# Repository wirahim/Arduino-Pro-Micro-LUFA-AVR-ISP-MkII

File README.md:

# Arduino Pro Micro LUFA AVR ISP MkII

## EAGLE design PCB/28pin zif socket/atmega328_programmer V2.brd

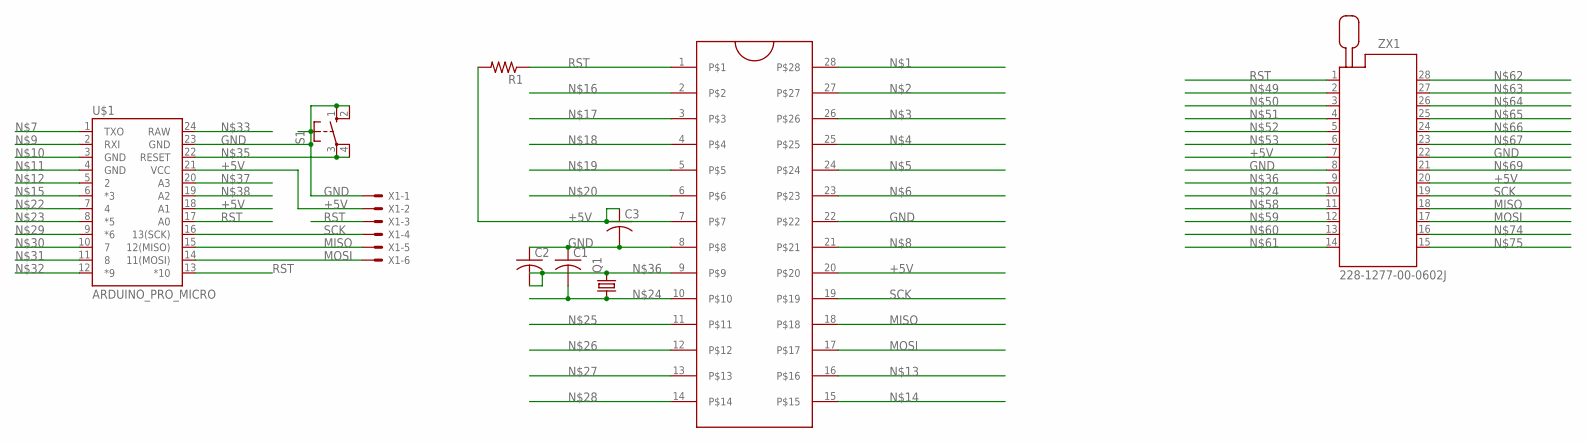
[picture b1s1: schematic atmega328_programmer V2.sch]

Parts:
C1, C2, C3: C-US025-024X044; C025-024X044
Q1: CRYSTALHC49U-V; HC49U-V
R1: R-US_0207/10; 0207/10
S1: 10-XX; B3F-10XX
U$1: ARDUINO_PRO_MICRO
U$2: ZIFSOCKET-28-3ZIFFSOCKET-28-3; DIL28-3-ZIF_SOCKET
X1: 22-23-2061
ZX1: 228-1277-00-0602J

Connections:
+5V: C3.1, R1.2, U$1.18 (A1), U$1.21 (VCC), U$2.7, U$2.20, X1.2, ZX1.7, ZX1.20
GND: C1.1, C2.1, C3.2, S1.1 (S), S1.2 (S1), U$1.23 (GND), U$2.8, U$2.22, X1.1, ZX1.8, ZX1.22
MISO: U$1.15 (12(MISO)), U$2.18, X1.5, ZX1.18
MOSI: U$1.14 (11(MOSI)), U$2.17, X1.6, ZX1.17
unnamed: C1.2, Q1.1, U$2.10, ZX1.10
unnamed: S1.3, S1.4 (P1), U$1.22 (RESET)
unnamed: C2.2, Q1.2, U$2.9, ZX1.9
RST: R1.1, U$1.13 (*10), U$1.17 (A0), U$2.1, X1.3, ZX1.1
SCK: U$1.16 (13(SCK)), U$2.19, X1.4, ZX1.19

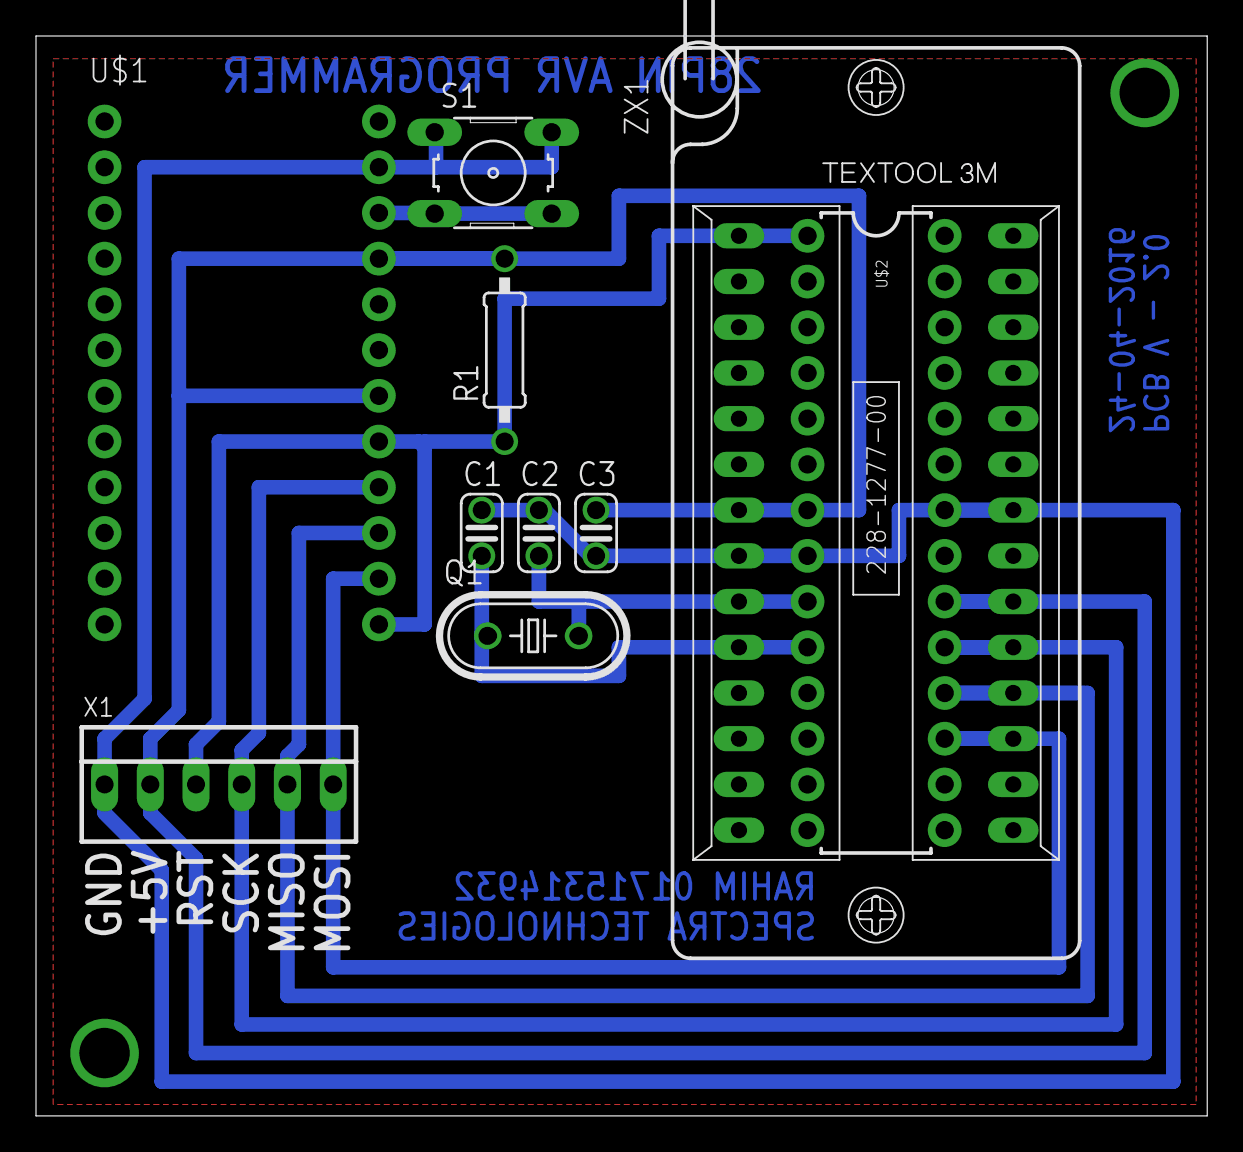
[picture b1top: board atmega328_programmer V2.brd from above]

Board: 2 copper layers, 65.1 x 60.0 mm, 10 parts (0 on the bottom side), 9 nets.

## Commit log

2022-03-12 Compiled binary for arduino pro micro
    upload code using avrdudess. programmer avr109 bootloader,
2022-03-28 pcb design

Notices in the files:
parts and their libraries:
SparkFun-Boards: Licensing: Creative Commons ShareAlike 4.0 International - https://creativecommons.org/licenses/by-sa/4.0
